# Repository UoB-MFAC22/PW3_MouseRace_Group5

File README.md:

# PW3_MouseRace_Group5
A Repo for tracking changes to Documents for Project Week 3

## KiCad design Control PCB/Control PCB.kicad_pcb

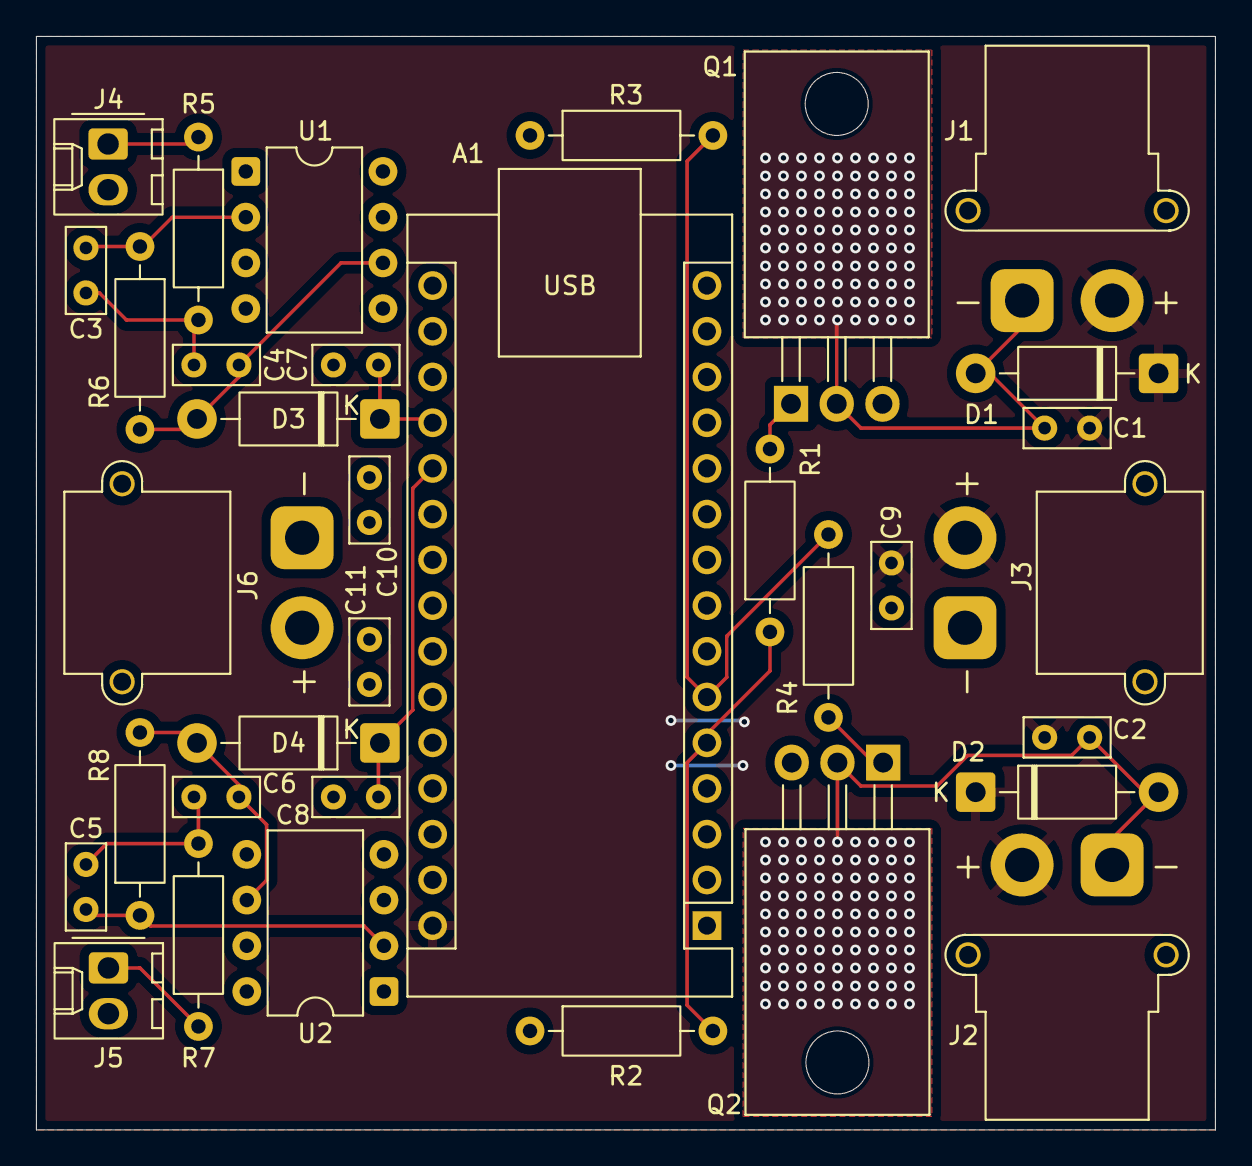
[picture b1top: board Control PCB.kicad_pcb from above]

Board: 4 copper layers, 65.5 x 60.8 mm, 34 parts (0 on the bottom side), 20 nets.

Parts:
A1: Arduino_Nano_ESP32; Arduino_Nano
C1, C2: 10n; C_Rect_L4.6mm_W2.0mm_P2.50mm_MKS02_FKP02
C3, C4, C5, C6: 0.22n; C_Rect_L4.6mm_W2.0mm_P2.50mm_MKS02_FKP02
C7, C8, C9, C10, C11: 10u; C_Rect_L4.6mm_W2.0mm_P2.50mm_MKS02_FKP02
D1, D2, D3, D4: 1N4001; D_DO-41_SOD81_P10.16mm_Horizontal
J1: L_Motor_XT30_F; AMASS_XT30PW-F_1x02_P2.50mm_Horizontal
J2: R_Motor_XT30_F; AMASS_XT30PW-F_1x02_P2.50mm_Horizontal
J3: Motor_Power_XT30_M; AMASS_XT30PW-M_1x02_P2.50mm_Horizontal
J4: Sense_L; Molex_KK-254_AE-6410-02A_1x02_P2.54mm_Vertical
J5: Sense_R; Molex_KK-254_AE-6410-02A_1x02_P2.54mm_Vertical
J6: Amp_power_XT30_M; AMASS_XT30PW-M_1x02_P2.50mm_Horizontal
Q1, Q2: IRLZ44N; TO-220-3_Horizontal_TabDown
R1, R4, R5, R7: 1K; R_Axial_DIN0207_L6.3mm_D2.5mm_P10.16mm_Horizontal
R2, R3, R6, R8: 10K; R_Axial_DIN0207_L6.3mm_D2.5mm_P10.16mm_Horizontal
U1, U2: TL071; DIP-8_W7.62mm

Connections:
+9V: C11.2, J6.2, U1.4 (V-), U2.4 (V-)
+BATT: A1.30 (VIN), C1.1, C2.1, C9.1, D1.1 (K), D2.1 (K), J1.2, J2.2, J3.2
-9V: C10.1, J6.1, U1.7 (V+), U2.7 (V+)
GND: A1.4 (GND), A1.29 (GND), C7.2, C8.2, C9.2, C10.2, C11.1, J3.1, J4.2, J5.2, Q1.3 (S), Q2.3 (S), R2.1, R3.1, U1.3 (+), U2.3 (+)
unnamed: C3.1, C4.1, R5.2
unnamed: C5.1, C6.2, R7.2
unnamed: C1.2, D1.2 (A), J1.1, Q1.2 (D)
unnamed: C2.2, D2.2 (A), J2.1, Q2.2 (D)
unnamed: C4.2, D3.2 (A), R6.2, U1.6
unnamed: C6.1, D4.2 (A), R8.2, U2.6
unnamed: J4.1, R5.1
unnamed: J5.1, R7.1
unnamed: Q1.1 (G), R1.2
unnamed: Q2.1 (G), R4.2
unnamed: C3.2, R6.1, U1.2 (-)
unnamed: C5.2, R8.1, U2.2 (-)
PWM_L: A1.5 (D2), R1.1, R2.2
PWM_R: A1.6 (D3), R3.2, R4.1
Sense_L: A1.19 (A0), C7.1, D3.1 (K)
Sense_R: A1.20 (A1), C8.1, D4.1 (K)

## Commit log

2026-03-16 Test and final code files
2026-03-16 Circuit Schematics and PCB
2026-03-16 Rename 20260312_PW3_MouseCode_v0.5.ino to PW3_MouseCode_v1.0.3
    Updated using new naming convention
2026-03-20 TheoFeren-Schematics-PCB-V2.0.1
    Added Usernames
2026-05-07 Update and rename PW3_MouseCode_v1.0.3 to PW3_MouseCode_v1.0.4
    Changed if loop thresholds and changed file name
2026-05-07 Update PW3_MouseCode_v1.0.4
    Lowered Sensor Thresholds
